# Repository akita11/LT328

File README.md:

# LED Tile328の関連ファイル。

## インストールと動作チェック

詳しい使い方は LT328man_v100.pdf を参照してください。以下は概要です。

1. ファイルをzipでダウンロード(右のほうの緑の"clone or Download"から)
2. ArduinoIDEから、スケッチ→ライブラリをインクルード→ZIP形式のライブラリをインストール、を選び、1.でダウンロードしたzipファイルを選ぶ。ライブラリに"LT328v2"が追加されていることを確認する
3. ArduinoIDEのツール→ボードから、"Arduino Pro or Pro Mini"を選び、プロセッサから"ATmega328(3.3V, 8MHz)"を選ぶ
4. LED TileとPCをmicroUSBケーブルで接続し、ArduinoIDEでシリアルポートを設定する
5. スケッチの例として"flow"を選び、コンパイルして転送すると、明るい光（レーザーポインタ光やスマホカメラのライトなど）があたったところのLEDが点灯し、本体を傾けるとその方向に模様が流れる ※使う加速度センサがMMA7660(LT328v2)の場合は、LT328v2.hでコメントアウトされている USE_MMA7660 のdefineを戻してください。ADXL345(LT328v3)の場合はそのままでOKです
6. Arduinoディレクトリ内のlibraries/LT328v2/board 以下に基板データが展開されますが、これは不要でしたら削除してください。

## ライブラリ関数の使い方

こちらを参照（※240803:サーバ設定の関係で現在閲覧できません。少々お待ち下さい）: https://ifdl.jp/akita/lt/

## お問い合わせ

使い方などについてのお問い合わせは、Junichi Akita (akita[at]ifdl.jp / @akita11)までご連絡ください。

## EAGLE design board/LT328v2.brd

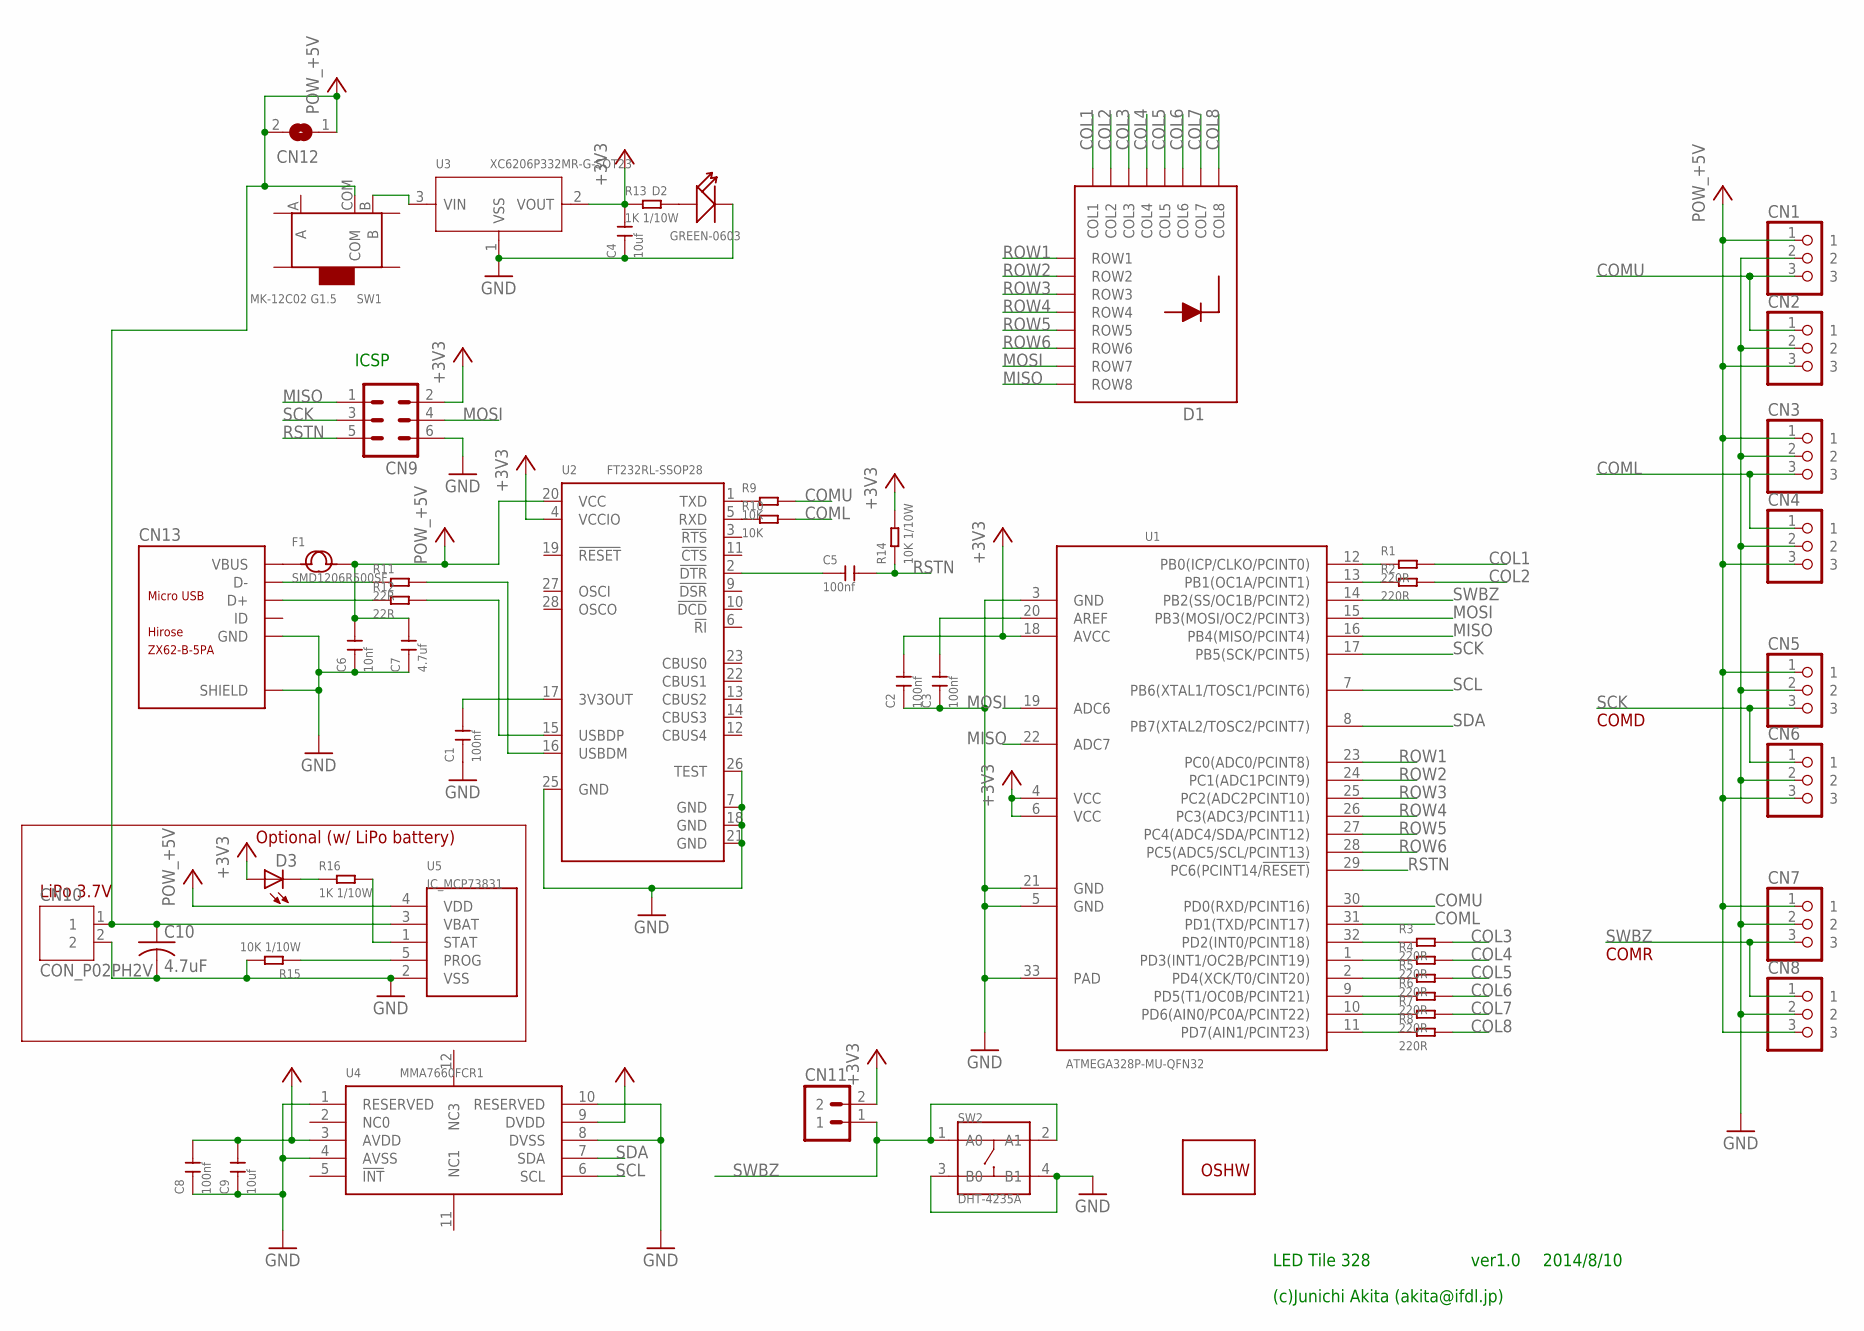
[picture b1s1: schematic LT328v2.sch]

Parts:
C1, C2, C3, C5, C8: 100nf; C0603
C4, C9: 10uf; C0805
C6: 10nf; C0603
C7: 4.7uf; C0603
C10: 4.7uF; C0603
CN1, CN2, CN3, CN4, CN5, CN6, CN7, CN8: CON_PINHD-1X3R; 1X03R
CN9: MA03-2
CN10: CON_P02PH2V; JST-PH2
CN11: CON_PINHD-1X2PTH; SPARKFUN_1X02
CN12: JUMPER_SJ
CN13: ZX62-B-5PA; MICRO-USB5+6P-SMD-0.65-AB
D1: LED_OSL641501BRA; TOM-1588BH
D2: GREEN-0603; LED-0603
D3: LED0603; SPARKFUN_LED-0603
F1: SMD1206R500SF; F1206
GOLD_ORB_SM1: OSHWLOGO_GOLD_ORB_SM; OSHW2
R1, R2, R3, R4, R5, R6, R7, R8: 220R; R0603
R9, R10: 10K; R0603
R11, R12: 22R; R0603
R13, R16: 1K 1/10W; R0603
R14, R15: 10K 1/10W; R0603
SW1: MK-12C02 G1.5; SW7-SMD-L6.7X2.7X3.2MM
SW2: DHT-4235A; SW4-SMD-4.2X3.2X2.5MM
U1: ATMEGA328P-MU-QFN32; QFN32G-0.5-5X5MM
U2: FT232RL-SSOP28; SSOP28-0.65-10.2X5.2MM
U3: XC6206P332MR-G-SOT23; SOT-23
U4: MMA7660FCR1; DFN10-0.5-3.0X3.0MM
U5: IC_MCP73831; SOT23-5L

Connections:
+3V3: C2.2, C4.2, C8.2, C9.2, CN9.2, CN11.2, D3.A, R13.1, R14.2, U1.4 (VCC), U1.6 (VCC), U1.18 (AVCC), U2.4 (VCCIO), U3.2 (VOUT), U4.3 (AVDD), U4.9 (DVDD)
+5V: C6.2, C7.2, C10.1, CN1.1, CN2.3, CN3.1, CN4.3, CN5.1, CN6.3, CN7.1, CN8.3, CN10.1, CN12.1, CN12.2, F1.2, SW1.COM, U2.20 (VCC), U5.3 (VBAT), U5.4 (VDD)
COL1: D1.P$13 (COL1), R1.2
COL2: D1.P$3 (COL2), R2.2
COL3: D1.P$4 (COL3), R3.2
COL4: D1.P$10 (COL4), R4.2
COL5: D1.P$6 (COL5), R5.2
COL6: D1.P$11 (COL6), R6.2
COL7: D1.P$15 (COL7), R7.2
COL8: D1.P$16 (COL8), R8.2
COML: CN3.3, CN4.1, R10.2, U1.31 (PD1(TXD/PCINT17))
COMU: CN1.3, CN2.1, R9.2, U1.30 (PD0(RXD/PCINT16))
GND: C1.1, C2.1, C3.1, C4.1, C6.1, C7.1, C8.1, C9.1, C10.2, CN1.2, CN2.2, CN3.2, CN4.2, CN5.2, CN6.2, CN7.2, CN8.2, CN9.6, CN10.2, CN13.5 (GND), CN13.P1 (SHIELD), CN13.P2 (SHIELD), CN13.P3 (SHIELD), CN13.P4 (SHIELD), CN13.P5 (SHIELD), CN13.P6 (SHIELD), D2.-, R15.2, SW2.3 (B0), SW2.4 (B1), U1.3 (GND), U1.5 (GND), U1.21 (GND), U1.33 (PAD), U2.7 (GND), U2.18 (GND), U2.21 (GND), U2.25 (GND), U2.26 (TEST), U3.1 (VSS), U4.1 (RESERVED), U4.4 (AVSS), U4.8 (DVSS), U4.10 (RESERVED), U5.2 (VSS)
MISO: CN9.1, D1.P$5 (ROW8), U1.16 (PB4(MISO/PCINT4)), U1.22 (ADC7)
MOSI: CN9.4, D1.P$2 (ROW7), U1.15 (PB3(MOSI/OC2/PCINT3)), U1.19 (ADC6)
unnamed: SW1.B, U3.3 (VIN)
unnamed: R11.2, U2.16 (USBDM)
unnamed: R12.2, U2.15 (USBDP)
unnamed: R9.1, U2.1 (TXD)
unnamed: C5.1, U2.2 (!DTR)
unnamed: C3.2, U1.20 (AREF)
unnamed: R10.1, U2.5 (RXD)
unnamed: D3.C, R16.1
unnamed: R16.2, U5.1 (STAT)
unnamed: C1.2, U2.17 (3V3OUT)
unnamed: D2.+, R13.2
unnamed: R8.1, U1.11 (PD7(AIN1/PCINT23))
unnamed: R7.1, U1.10 (PD6(AIN0/PC0A/PCINT22))
unnamed: R6.1, U1.9 (PD5(T1/OC0B/PCINT21))
unnamed: R5.1, U1.2 (PD4(XCK/T0/CINT20))
unnamed: R4.1, U1.1 (PD3(INT1/OC2B/PCINT19))
unnamed: R3.1, U1.32 (PD2(INT0/PCINT18))
unnamed: R1.1, U1.12 (PB0(ICP/CLKO/PCINT0))
unnamed: R2.1, U1.13 (PB1(OC1A/PCINT1))
unnamed: CN13.2 (D-), R11.1
unnamed: CN13.3 (D+), R12.1
unnamed: R15.1, U5.5 (PROG)
ROW1: D1.P$9 (ROW1), U1.23 (PC0(ADC0/PCINT8))
ROW2: D1.P$14 (ROW2), U1.24 (PC1(ADC1PCINT9))
ROW3: D1.P$8 (ROW3), U1.25 (PC2(ADC2PCINT10))
ROW4: D1.P$12 (ROW4), U1.26 (PC3(ADC3/PCINT11))
ROW5: D1.P$1 (ROW5), U1.27 (PC4(ADC4/SDA/PCINT12))
ROW6: D1.P$7 (ROW6), U1.28 (PC5(ADC5/SCL/PCINT13))
RSTN: C5.2, CN9.5, R14.1, U1.29 (PC6(PCINT14/!RESET))
SCK: CN5.3, CN6.1, CN9.3, U1.17 (PB5(SCK/PCINT5))
SCL: U1.7 (PB6(XTAL1/TOSC1/PCINT6)), U4.6 (SCL)
SDA: U1.8 (PB7(XTAL2/TOSC2/PCINT7)), U4.7 (SDA)
SWBZ: CN7.3, CN8.1, CN11.1, SW2.1 (A0), SW2.2 (A1), U1.14 (PB2(SS/OC1B/PCINT2))
VBUS: CN13.1 (VBUS), F1.1

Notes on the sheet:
ICSP
LiPo 3.7V
ver1.0
2014/8/10
(c)Junichi Akita (akita@ifdl.jp)
LED Tile 328
COMD
COMR
Optional (w/ LiPo battery)

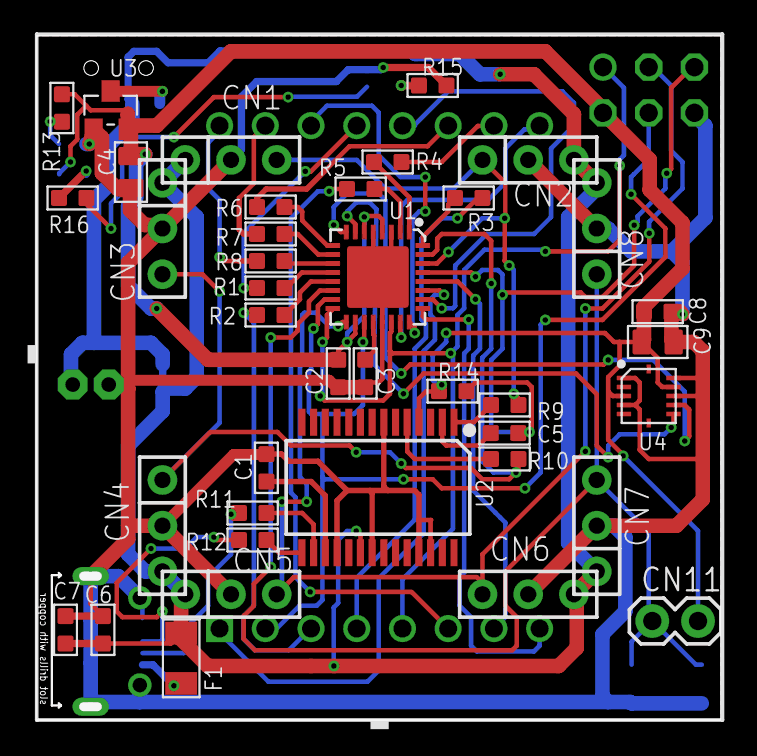
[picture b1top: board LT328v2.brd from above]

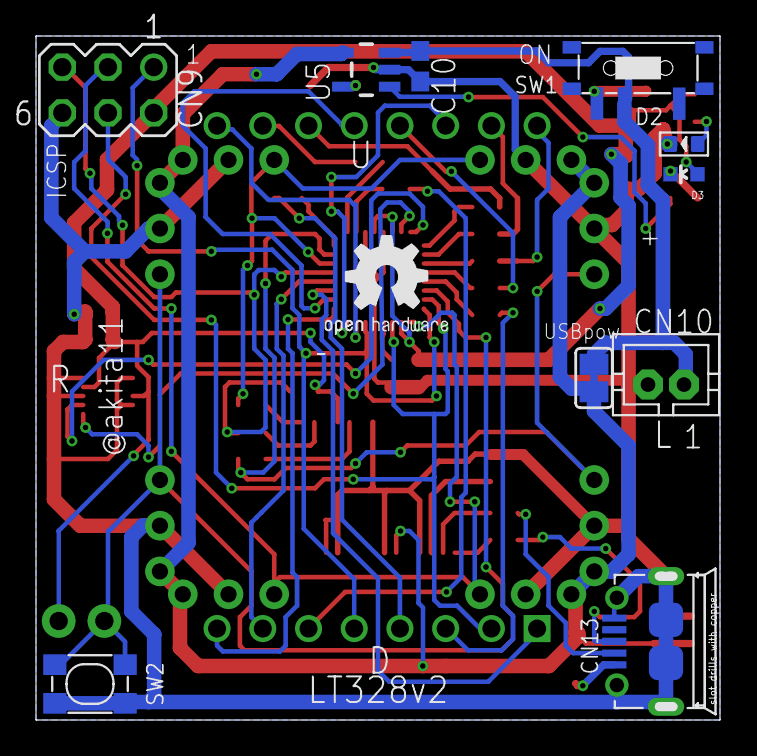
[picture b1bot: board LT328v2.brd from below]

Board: 2 copper layers, 38.0 x 38.0 mm, 51 parts (11 on the bottom side), 49 nets.

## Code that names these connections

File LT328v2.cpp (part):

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void LT::set_port_dir(int pos, int num, int dir)
{
//  for BRA
//  - Col1-8(Cathode) : PB0-1/PD2-7 (via 270ohm)
//  - Row1-8(Anode)   : PC0-5/PB3-4 (ADC0-7)
  if (pos == PORT_ROW){
    if (dir == PORT_OUT){
      if (num > 7){DDRC |= 0x3f; DDRB |= 0x18;}
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void LT::set_port_value(int pos, int num, int value)
{
//  for BRA
//  - Col1-8(Cathode) : PB0-1/PD2-7 (via 270ohm)
//  - Row1-8(Anode)   : PC0-5/PB3-4 (ADC0-7)
  if (pos == PORT_ROW){
    if (value == 1){
      if (num > 7){PORTC |= 0x3f; PORTB |= 0x18;}
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void LT::com_set_dir(uint8_t dir, uint8_t md)
{

  // COMU=PD0 COMD=PB5 COML=PD1 COMR=PB2
  if (md == COM_TX){
    switch (dir){
      case COMU: PORTD |= 0x01; DDRD |= 0x01; break;
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uint8_t LT::com_read_pin(uint8_t dir)
{
  switch (dir){
    case COMU: if (PIND & 0x01) return(1); else return(0); break;
    case COMD: if (PINB & 0x20) return(1); else return(0); break;
    case COML: if (PIND & 0x02) return(1); else return(0); break;
    case COMR: if (PINB & 0x04) return(1); else return(0); break;
  }
}
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#define SDA_IN()  {}
#define SDA_OUT() {}

// SCL=PB6 SDA=PB7
void LT::setSDA(uint8_t x)
{
  if (x == 0){
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
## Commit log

2017-04-11 readmeの追加
2017-04-11 readmeの追記
2017-04-11 readmeの誤字を修正
2017-04-11 readmeを修正（いったん削除）
2017-04-11 不要ファイルの整理、readmeの再追加
2017-04-11 readmeの整形
2017-04-11 基板データの追加
2017-04-17 マニュアルの追加
2017-04-24 マニュアルの説明の補足を追記
2017-04-24 マニュアルの微調整。
2021-06-07 デフォルトの加速度センサをADXL345に変更
    MMA7660を使う場合は、LT328v2.hの USE_MMA7660 のdefineを戻す
2021-06-07 使う加速度センサについてREADME.mdに追記
2021-06-07 flow.inoを修正。SWでリセットを追加
2021-06-07 README.mdの連絡先表記を修正

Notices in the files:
LT328v2.cpp:
Copyright 2012 akita11 (akita@ifdl.jp). All right reserved
Copyright 2010 arms22. All right reserved.
